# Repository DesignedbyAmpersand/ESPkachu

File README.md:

https://www.reddit.com/r/SBCGaming/comments/13wpaec/this_is_espkachu

It’s an ESP32 inside a broken Pocket Pikachu. It uses Nathalis’s NCAT software to play NES, GBC, and SMS on a 1.3” IPS screen. There’s a 100mAh battery crammed in there that lasts 16 minutes, and it’s recharged via a tiny external PCB because I didn’t want to cut a massive hole for a USB C socket. The SD card can be accessed by unscrewing the battery cover. It uses all but 1 of the original screws with a bunch of the inside carved away to make space.

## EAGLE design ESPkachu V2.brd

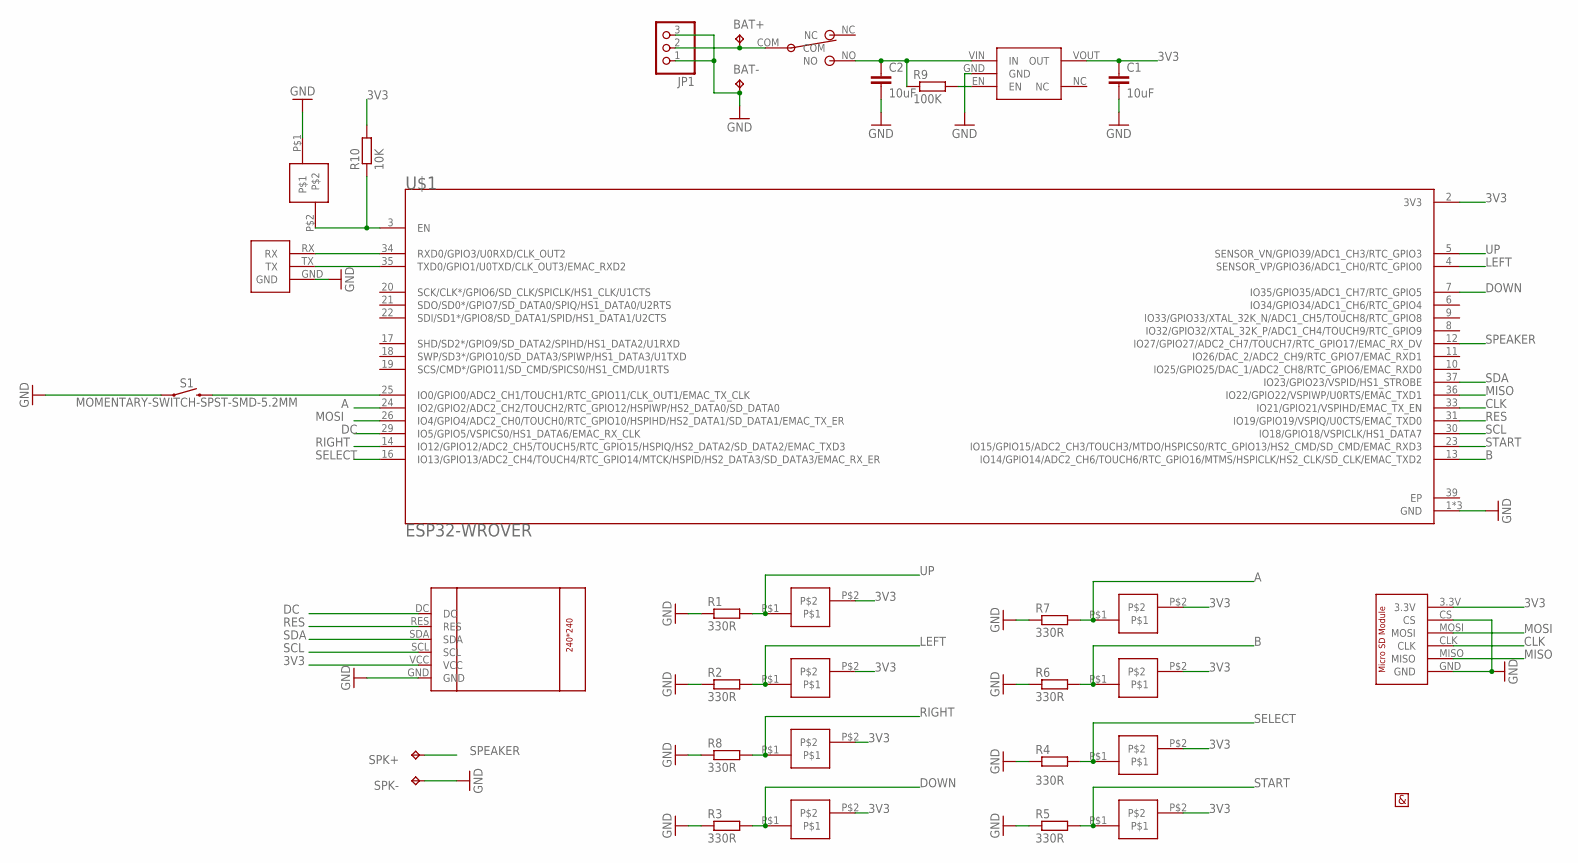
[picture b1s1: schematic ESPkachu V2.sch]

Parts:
A: ESPKACHU-PAD
B: ESPKACHU-PAD
BAT+: TPTP20R; TP20R
BAT-: TPTP20R; TP20R
C1, C2: 10uF; C0805
DOWN: ESPKACHU-PAD
JP1: PINHD-1X03_2.54-S; 1X03-S
LEFT: ESPKACHU-PAD
R1, R2, R3, R4, R5, R6, R7, R8: 330R; M0805
R9: 100K; M0805
R10: 10K; M0805
RESET: ESPKACHU-PAD
RIGHT: ESPKACHU-PAD
S1: MOMENTARY-SWITCH-SPST-SMD-5.2MM; TACTILE_SWITCH_SMD_5.2MM
SELECT: ESPKACHU-PAD
SPK+: TPTP20R; TP20R
SPK-: TPTP20R; TP20R
START: ESPKACHU-PAD
U$1: ESP32-WROVER; XCVR-ESP32-WROVER
U$2: LCD-ST7789-1.3INCH
U$3: ESPRESSO-MICROSD-MODULE
U$4: SS12D00-SWITCH
U$5: AMP-HALF
U$6: AP2112-REGULATOR; SOT25
U$7: ESPKACHU-UART
UP: ESPKACHU-PAD

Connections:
3V3: A.P$2, B.P$2, C1.1, DOWN.P$2, LEFT.P$2, R10.2, RIGHT.P$2, SELECT.P$2, START.P$2, U$1.2 (3V3), U$2.VCC, U$3.3.3V, U$6.VOUT (OUT), UP.P$2
A: A.P$1, R7.2, U$1.24 (IO2/GPIO2/ADC2_CH2/TOUCH2/RTC_GPIO12/HS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)
B: B.P$1, R6.2, U$1.13 (IO14/GPIO14/ADC2_CH6/TOUCH6/RTC_GPIO16/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)
CLK: U$1.33 (IO21/GPIO21/VSPIHD/EMAC_TX_EN), U$3.CLK
DC: U$1.29 (IO5/GPIO5/VSPICS0/HS1_DATA6/EMAC_RX_CLK), U$2.DC
DOWN: DOWN.P$1, R3.2, U$1.7 (IO35/GPIO35/ADC1_CH7/RTC_GPIO5)
EP: U$1.39 (EP)
GND: BAT-.TP, C1.2, C2.2, JP1.1, JP1.3, R1.1, R2.1, R3.1, R4.1, R5.1, R6.1, R7.1, R8.1, RESET.P$1, S1.1, S1.2 (1), SPK-.TP, U$1.1 (GND), U$1.15 (GND), U$1.38 (GND), U$2.GND, U$3.CS, U$3.GND, U$6.GND, U$7.GND
LEFT: LEFT.P$1, R2.2, U$1.4 (SENSOR_VP/GPIO36/ADC1_CH0/RTC_GPIO0)
MISO: U$1.36 (IO22/GPIO22/VSPIWP/U0RTS/EMAC_TXD1), U$3.MISO
MOSI: U$1.26 (IO4/GPIO4/ADC2_CH0/TOUCH0/RTC_GPIO10/HS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), U$3.MOSI
unnamed: R9.2, U$6.EN
unnamed: C2.1, R9.1, U$4.NO, U$6.VIN (IN)
unnamed: R10.1, RESET.P$2, U$1.3 (EN)
unnamed: S1.3 (2), S1.4 (2), U$1.25 (IO0/GPIO0/ADC2_CH1/TOUCH1/RTC_GPIO11/CL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)
unnamed: U$1.34 (RXD0/GPIO3/U0RXD/CLK_OUT2), U$7.RX
unnamed: U$1.35 (TXD0/GPIO1/U0TXD/CLK_OUT3/EMAC_RXD2), U$7.TX
unnamed: BAT+.TP, JP1.2, U$4.COM
RES: U$1.31 (IO19/GPIO19/VSPIQ/U0CTS/EMAC_TXD0), U$2.RES
RIGHT: R8.2, RIGHT.P$1, U$1.14 (IO12/GPIO12/ADC2_CH5/TOUCH5/RTC_GPIO15/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)
SCL: U$1.30 (IO18/GPIO18/VSPICLK/HS1_DATA7), U$2.SCL
SDA: U$1.37 (IO23/GPIO23/VSPID/HS1_STROBE), U$2.SDA
SELECT: R4.2, SELECT.P$1, U$1.16 (IO13/GPIO13/ADC2_CH4/TOUCH4/RTC_GPIO14/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)
SPEAKER: SPK+.TP, U$1.12 (IO27/GPIO27/ADC2_CH7/TOUCH7/RTC_GPIO17/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)
START: R5.2, START.P$1, U$1.23 (IO15/GPIO15/ADC2_CH3/TOUCH3/MTDO/HSPICS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)
UP: R1.2, U$1.5 (SENSOR_VN/GPIO39/ADC1_CH3/RTC_GPIO3), UP.P$1

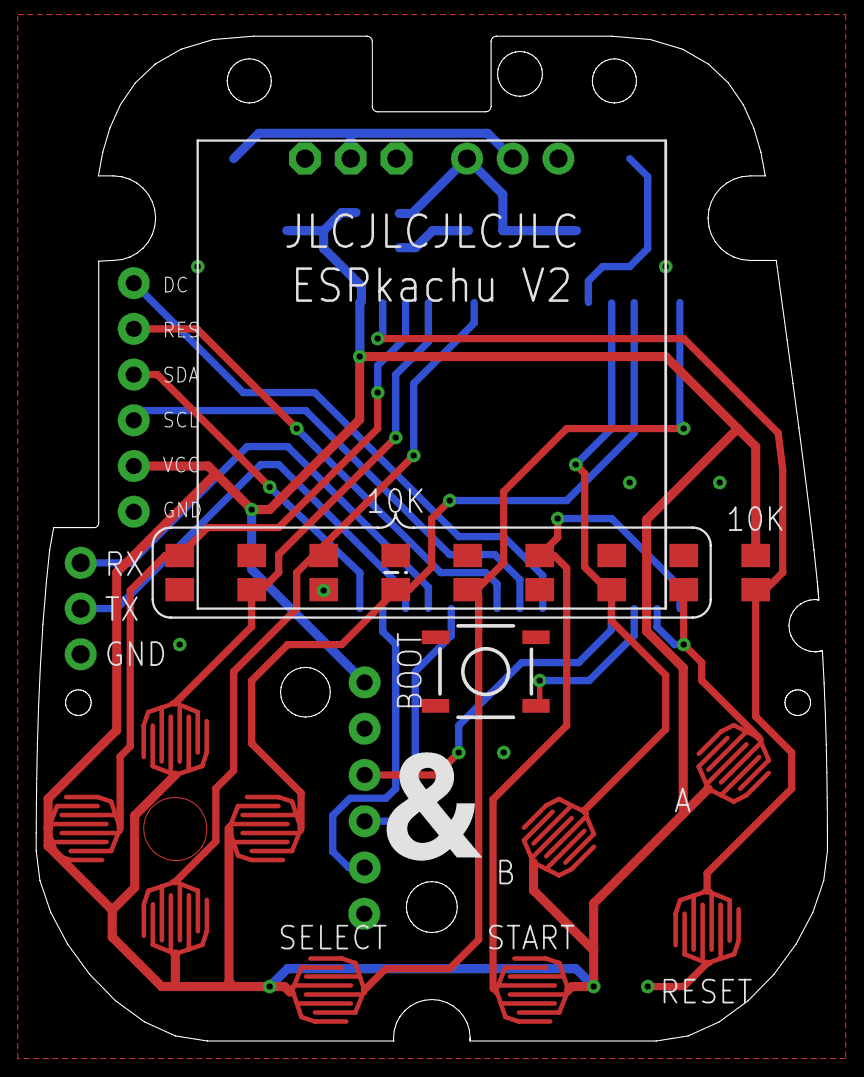
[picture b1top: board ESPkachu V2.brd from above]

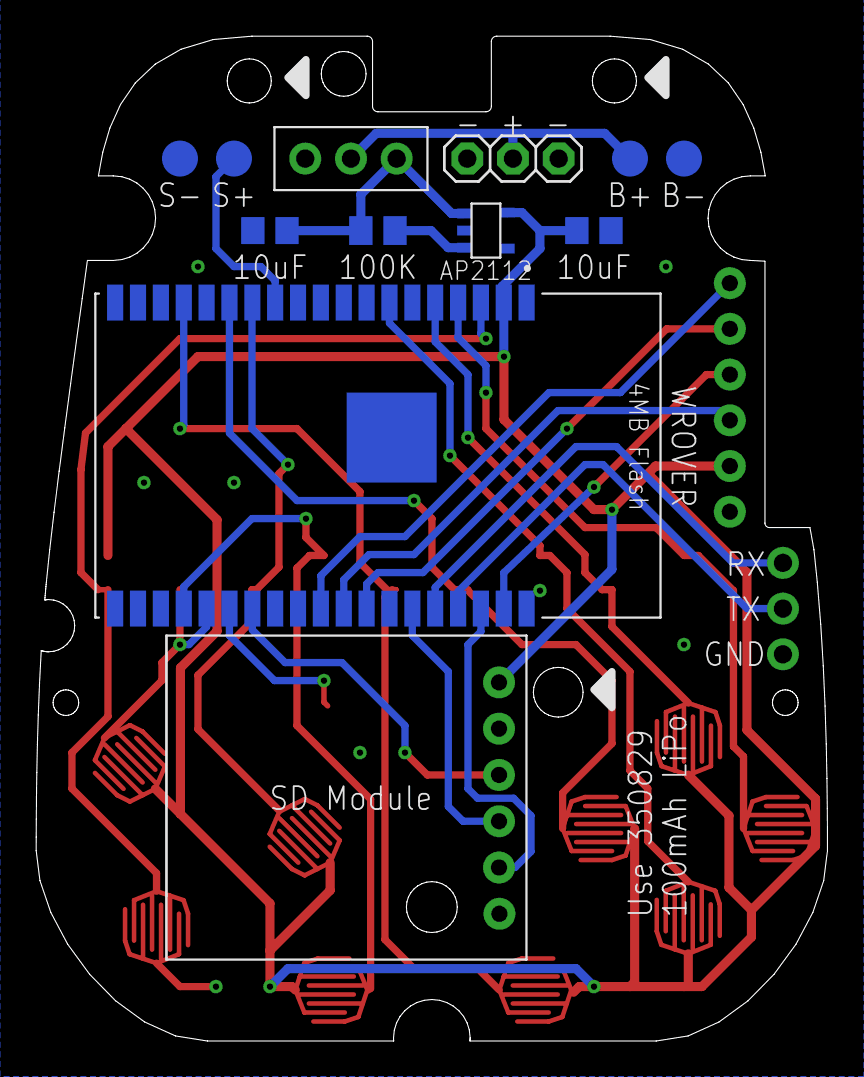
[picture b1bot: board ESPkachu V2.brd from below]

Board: 2 copper layers, 44.0 x 55.8 mm, 34 parts (13 on the bottom side), 25 nets.

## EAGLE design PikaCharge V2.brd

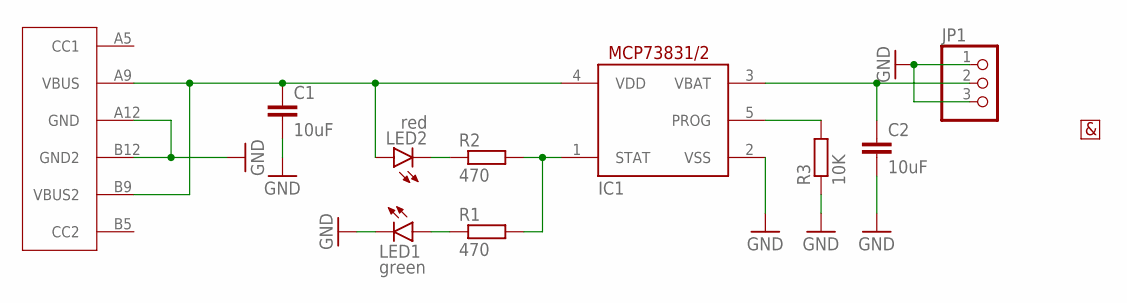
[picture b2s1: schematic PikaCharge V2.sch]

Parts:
C1, C2: 10uF; C0805
IC1: MCP73831/OT; SOT23-5L
JP1: PINHD-1X03_2.54-S; 1X03-S
LED1: green; CHIP-LED0805
LED2: red; CHIP-LED0805
R1, R2: 470; R0805
R3: 10K; R0805
U$1: USB-C-6PIN
U$2: AMP-HALF

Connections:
GND: C1.2, C2.2, IC1.2 (VSS), JP1.1, JP1.3, LED1.C, R3.1, U$1.A12 (GND), U$1.B12 (GND2)
unnamed: IC1.5 (PROG), R3.2
unnamed: IC1.1 (STAT), R1.2, R2.2
unnamed: LED2.C, R2.1
unnamed: LED1.A, R1.1
unnamed: C1.1, IC1.4 (VDD), LED2.A, U$1.A9 (VBUS), U$1.B9 (VBUS2)
unnamed: C2.1, IC1.3 (VBAT), JP1.2

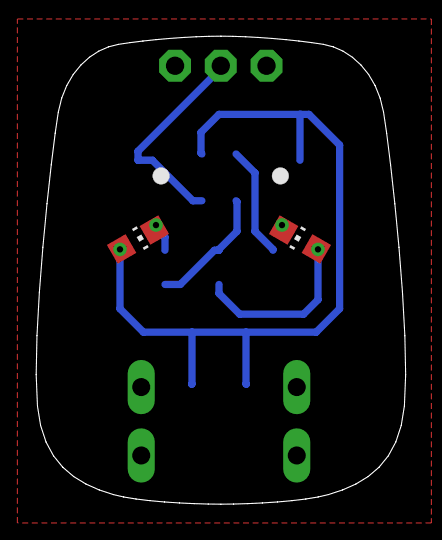
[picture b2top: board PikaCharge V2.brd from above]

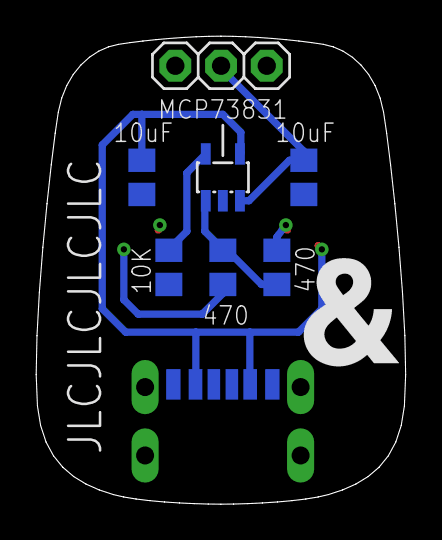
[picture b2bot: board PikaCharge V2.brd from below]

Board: 2 copper layers, 20.5 x 26.0 mm, 11 parts (9 on the bottom side), 7 nets.

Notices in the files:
parts and their libraries:
SparkFun-Switches: Licensing: Creative Commons ShareAlike 4.0 International - https://creativecommons.org/licenses/by-sa/4.0
